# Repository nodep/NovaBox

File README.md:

# NovaBox

This repo contains circuit and PCB designs for Bluetooth amplifiers

### Why build yet another Bluetooth speaker?

The main motivation for this project was the fact that I needed a Bluetooth speaker with batteries that are easy to remove and replace. Most of the commercial Bluetooth speakers have a charging port, and when you run out of battery power the device has to be connected to a charger for several hours. With removable batteries it takes ten seconds to go from empty to full if you have a spare battery. Even though CSR8635 needs only a few components to be able to charge Li-ion batteries, an integrated charger would make the PCB larger, there would be problems with heat dissipation during charging, and charging a medium capacity 18650 battery would take too long.

## The circuit

The circuit is based around the CSR8635 module you can get on most Chinese on-line shops. Its model number is BT835.

### Schematic and PCB

The circuit and PCB are designed in KiCad v5. The project contains all the symbols in its own symbol library (NovaBox.lib) and all the footprints (NovaBox.pretty). The schematic only references power symbols (GND, VCC, Batt, 5V) from the KiCad libraries. The circuit schematic is also saved in PDF [here](docs/NovaBox_8635.pdf).

The PCB has two layers with components soldered on both sides.

### Circuit sections

The circuit has several subsections:

* A single unprotected Li-ion 18650 battery with reverse protection and reverse indicator LED, and a hard on/off switch brought out to a pin header.
* The CSR8635 module with five buttons brought out to pin headers, an RGD LED driven from the module's 3 LED pins, and CSR8635's USB pins brought out to a THT Mini USB connector. The buttons can be configured for any of the standard commands: play/pause, next, volume up/down and so on.
* A section providing a pulse on CSR8635's PWER_E pin which wakes it up after the circuit has received power.
* The power section with an [LT1308](docs/LT1308abfb.pdf) DC/DC converter which boost the battery voltage to 5V at max 1A. The power section is disabled when CSR8635 goes to shutdown on low battery (< 3.2V). LT1308 has a soft-start feature which is implemented in the design, but is not necessary for the operation of the rest of the power section.
* A four level battery charge indicator with four LEDs which is built around a quad op-amp [MCP6004](docs/MCP6004.pdf). The op-amps work as comparators with inputs from four voltage dividers, comparing them to a 2.5V reference [LM4040](docs/lm4040-n.pdf). The op-amp outputs drive the four LEDs.
* The audio amplifier section is built around two [PAM8304](docs/PAM8304.pdf). The amplifiers can drive two 8Ω speakers at 1.7W each. They can also drive 4Ω speakers at 3W each, but the sum power requirement of the amplifiers would exceed the 5W that LT1308 can provide.
 
## Flash configuration

The SPI configuration interface of the CSR8635 module is brought out to a 5 pin header. This can be used to configure various parameters of the system such as device name, button mapping, RGB LED states, etc.

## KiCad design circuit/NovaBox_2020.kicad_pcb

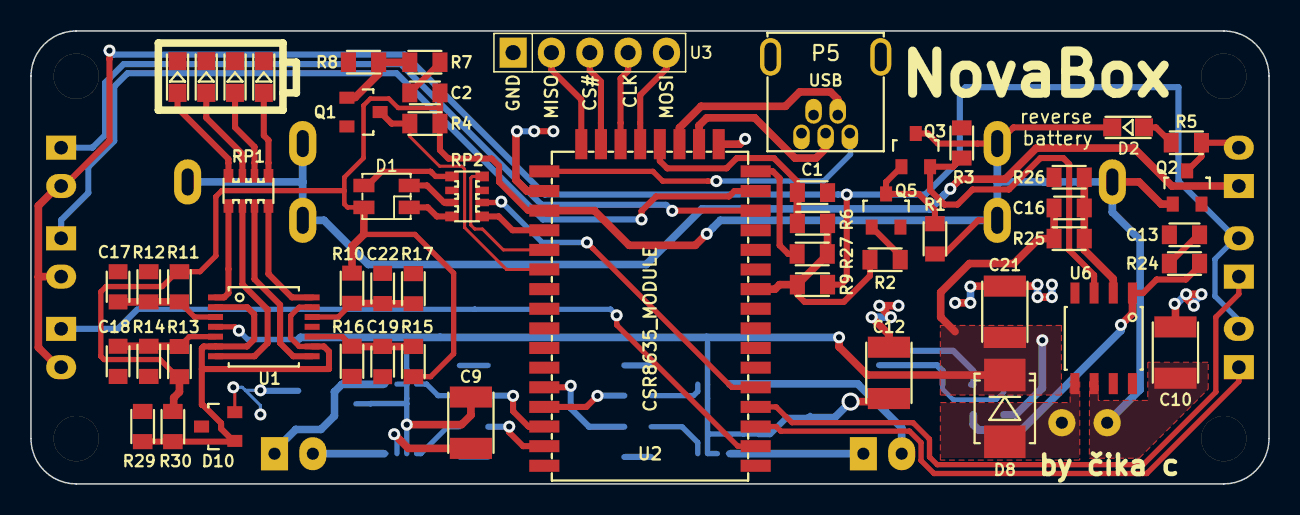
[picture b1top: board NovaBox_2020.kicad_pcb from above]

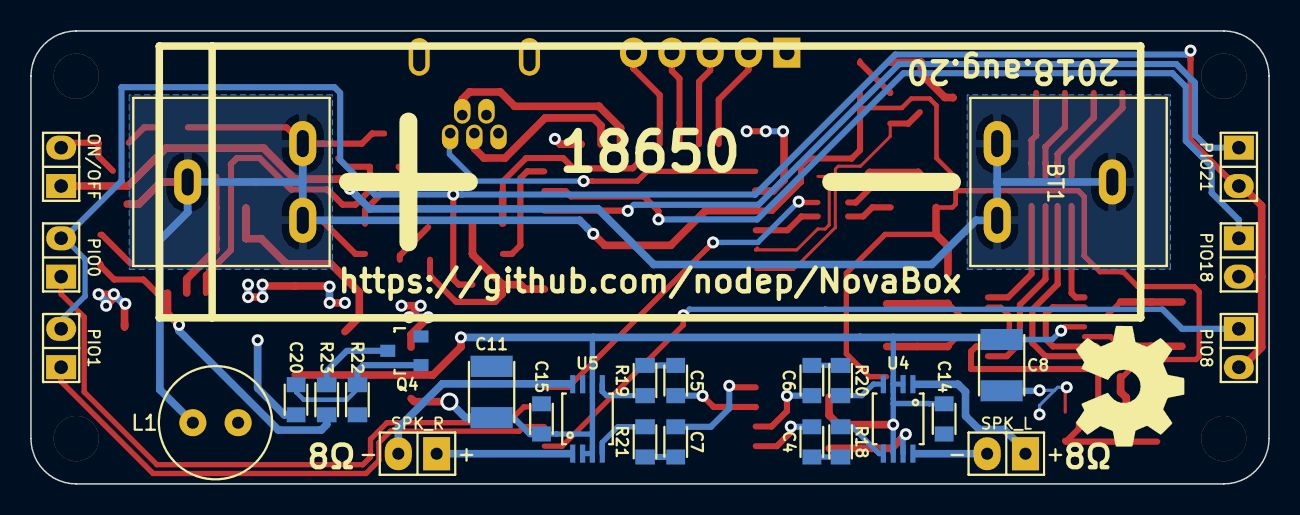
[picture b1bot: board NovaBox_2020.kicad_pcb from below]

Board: 2 copper layers, 82.0 x 30.0 mm, 86 parts (28 on the bottom side), 69 nets.

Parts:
BT1: 18650; Batt_Holder_18650
C1: 100nF; C_0805
C2, C4, C5, C6, C7, C14, C15, C17, C18, C19, C22: 1uF; C_0805
C8, C9, C10, C11, C12, C21: 47uF; C_1210
C13: 100pF; C_0805
C16: 330pF; C_0805
C20: 33nF; C_0805
D1: LED_RABG; PLCC4
D2: REVERSE_BATT; LED_0805
D4: BATT_E; LED_0805
D5: BATT_L; LED_0805
D6: BATT_M; LED_0805
D7: BATT_H; LED_0805
D8: MBRS130LT3; SMB_403A
D10: Vref 2.5V; SOT-23
L1: 4.7uH; COIL0608
P1, P2, P3, P4: MH; MountingHole
P5: USB; USB_MiniB_THT
Q1, Q4, Q5: MMBT3904; SOT-23
Q2: IRLML6344; SOT-23
Q3: IRLML6401; SOT-23
R1, R2, R3, R4, R6, R8, R18, R19, R20, R21, R27, R29: 10K; R_0805
R5, R7, R9: 1K; R_0805
R10, R13: 270K; R_0805
R11, R15: 240K; R_0805
R12, R14: 620K; R_0805
R16, R17: 470K; R_0805
R22, R23: 33K; R_0805
R24: 47K; R_0805
R25: 316K; R_0805
R26: 100K; R_0805
R30: 750; R_0805
RP1, RP2: R_Pack04; Resistor_Array_x4_1206
S1: SPK_L; SPKR
S2: SPK_R; SPKR
SW1: PIO18; Switch_2.5mm
SW2: PIO21; Switch_2.5mm
SW3: PIO8; Switch_2.5mm
SW4: PIO0; Switch_2.5mm
SW5: PIO1; Switch_2.5mm
SW6: ON/OFF; Switch_2.5mm
U1: MCP6004; TSSOP-14_4.4x5mm_Pitch0.65mm
U2: CSR8635_MODULE
U3: CSR_DebugSmall
U4, U5: PAM8304; MSOP-8_0.65mmPitch
U6: LT1308; SOIC-8_3.9x4.9mm_Pitch1.27mm

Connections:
1V8: R2.2, R6.1, R9.1, R27.1, U2.10
2V5: D10.1, R29.2, R30.1, U1.2, U1.6, U1.9, U1.13
+5V: C8.1, C9.1, C11.1, C12.1, C14.1, C15.1, C16.1, C20.2, C21.1, D8.1, R25.1, U1.4, U4.2, U4.3, U4.6, U5.2, U5.3, U5.6
+BATT: BT1.1, C2.1, C10.1, D1.2, D2.1, L1.2, Q2.1, Q3.3, R1.1, R4.2, R10.2, R11.2, R13.2, R15.2, R30.2, U2.27, U6.6
/-BATT: BT1.2, SW6.1
/D+: P5.3, U2.18
/D-: P5.2, U2.19
/FB: C16.2, R25.2, R26.1, U6.2
/SW: D8.2, L1.1, U6.5
CSR_RST: C1.1, R6.2, U2.20
GND: C1.2, C8.2, C9.2, C10.2, C11.2, C12.2, C13.2, C14.2, C15.2, C17.2, C18.2, C19.2, C21.2, C22.2, D4.1, D5.1, D6.1, D7.1, D10.2, P5.5, Q1.2, Q2.2, Q4.2, Q5.2, R3.2, R8.1, R12.2, R14.2, R16.2, R17.2, R22.2, R26.2, R29.1, U1.11, U2.17, U2.26, U2.40, U3.5, U4.7, U5.7, U6.4
LED0: RP2.1, U2.28
LED1: RP2.2, U2.5
LED2: RP2.4, U2.29
unnamed: C2.2, R7.2
unnamed: C4.1, R18.1
unnamed: C4.2, U2.39
unnamed: C5.1, R19.1
unnamed: C5.2, U2.37
unnamed: C6.1, R20.1
unnamed: C6.2, U2.38
unnamed: C7.1, R21.1
unnamed: C7.2, U2.36
unnamed: C13.1, R24.2
unnamed: C17.1, R11.1, R12.1, U1.3
unnamed: C18.1, R13.1, R14.1, U1.5
unnamed: C19.1, R15.1, R16.1, U1.10
unnamed: C20.1, Q4.1, R22.1
unnamed: C22.1, R10.1, R17.1, U1.12
unnamed: D1.1, RP2.8
unnamed: D1.3, RP2.5
unnamed: D1.4, RP2.7
unnamed: D2.2, R5.2
unnamed: D4.2, RP1.8
unnamed: D5.2, RP1.7
unnamed: D6.2, RP1.6
unnamed: D7.2, RP1.5
unnamed: Q1.1, R7.1, R8.2
unnamed: Q2.3, R5.1, SW6.2
unnamed: Q3.1, Q5.3, R1.2
unnamed: Q4.3, R23.2
unnamed: Q5.1, R2.1
unnamed: R9.2, SW1.2, SW2.2, SW3.2, SW4.2, SW5.2
unnamed: R18.2, U4.5
unnamed: R19.2, U5.5
unnamed: R20.2, U4.4
unnamed: R21.2, U5.4
unnamed: R23.1, R24.1, U6.1
unnamed: RP1.1, U1.1
unnamed: RP1.2, U1.7
unnamed: RP1.3, U1.8
unnamed: RP1.4, U1.14
unnamed: S1.1, U4.1
unnamed: S1.2, U4.8
unnamed: S2.1, U5.1
unnamed: S2.2, U5.8
unnamed: U2.21, U3.1
unnamed: U2.22, U3.2
unnamed: U2.23, U3.3
unnamed: U2.24, U3.4
PIO0: SW4.1, U2.4
PIO1: SW5.1, U2.3
PIO8: SW3.1, U2.2
PIO18: SW1.1, U2.15
PIO21: SW2.1, U2.14
PWER_E: Q1.3, R4.1, U2.30
SPI_PCM: R27.2, U2.16
VBUS: P5.1, U2.25
VR_SHDN: Q3.2, R3.1, U6.3

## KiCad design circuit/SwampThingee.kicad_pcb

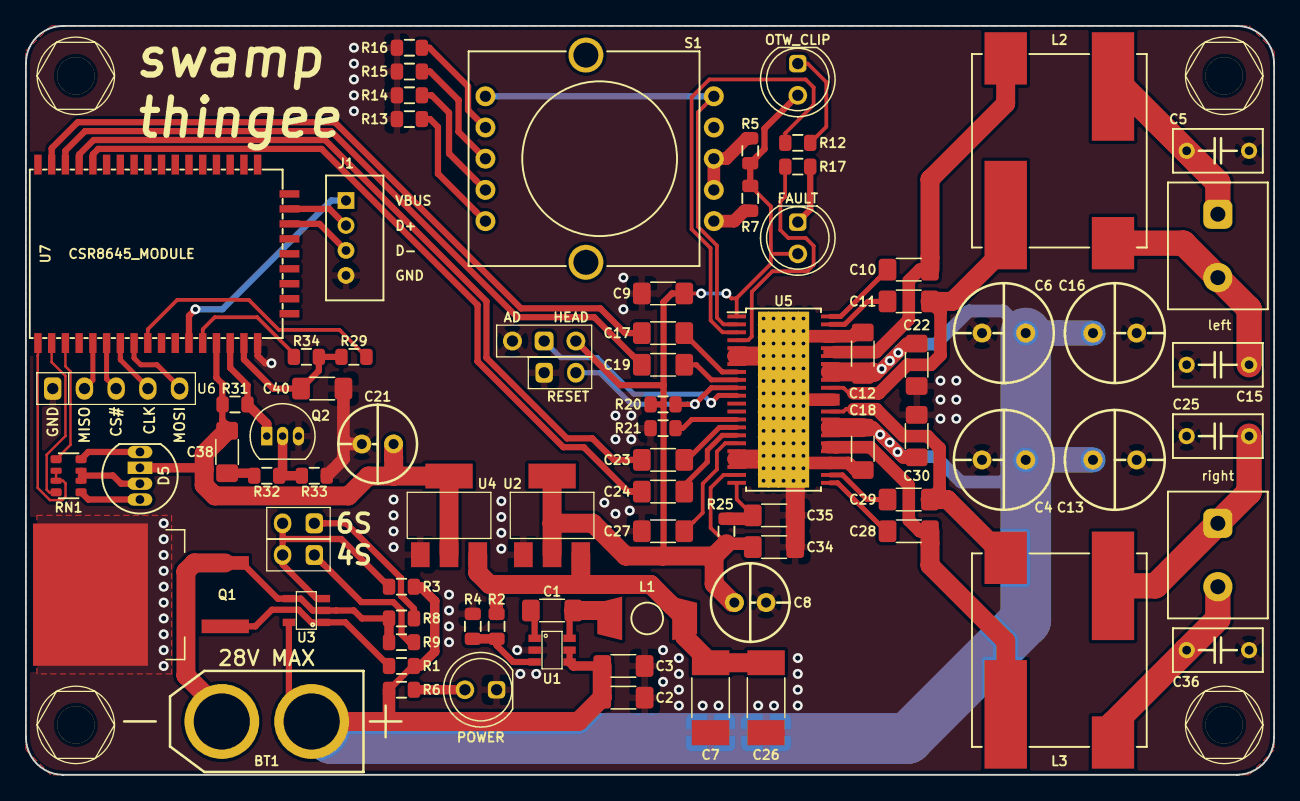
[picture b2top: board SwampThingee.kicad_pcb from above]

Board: 2 copper layers, 100.0 x 60.0 mm, 86 parts (0 on the bottom side), 69 nets.

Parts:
BT1: 28V MAX; XT60-M-NO_PM
C1, C3, C9, C40: 100nF; C_1206
C2: 4.7μF; C_1206
C4, C6, C13, C16: 470μF; CPOL_D8_P3.5
C5, C15, C25, C36: 1μF; C_FILM_5MM
C7, C26: 15μF; C_1812
C8: 470μF; CPOL_D6.3_P2.5
C10, C11, C27, C28, C29: 33nF; C_1206
C12, C17, C18, C19, C22, C23, C24, C30, C34, C35, C38: 1μF; C_1206
C21: 100μF; CPOL_D6.3_P2.5
D2: OTW_CLIP; LED_D5.0mm
D3: POWER; LED_D5.0mm
D4: FAULT; LED_D5.0mm
D5: LED_RABG; LED_D5.0mm_RGB
J1: CONN_01X04; PIN_1x4_P2.00mm
J2, J3, J4, J5: HOLE; MountingHole
L1: 68μH; COIL_SRR6603
L2, L3: 10μH; COILCRAFT-UA801x-AL
Q1: IRFS52N15DTRLP; TO-263-2
Q2: BC547; TO-92_Inline_Narrow_Oval
R1, R6, R29, R31, R33, R34: 10K; R_0805
R2: 133K; R_0805
R3: 1.69M; R_0805
R4: 22.1K; R_0805
R5: 100K; R_0805
R7: 75K; R_0805
R8: 105K; R_0805
R9: 162K; R_0805
R12, R17, R32: 1K; R_0805
R13: 5.6K; R_0805
R14: 20K; R_0805
R15: 39K; R_0805
R16, R20: 47K; R_0805
R21: 50K; R_0805
R25: 3.3R; R_0805
RN1: 1K; Resistor_Array_x4_1206
S1: GAIN_SEL; SR1712F-0204-20F0A-N9-N-027
SPK1: left; SPKR_5MM_BLUE
SPK2: right; SPKR_5MM_BLUE
SW1: RESET; Switch_2.5mm
SW3: HEAD/AD; SW_SPDT_JUMPER
SW9: 6S; Switch_2.5mm
SW10: 4S; Switch_2.5mm
U1: TPS560430; SOT-23-6
U2: LM1117-5.0; SOT-223
U3: MAX6457; SOT-23-5
U4: LM1117-3.3; SOT-223
U5: TPA3220; TSSOP-44_4.4x9.7mm_Pitch0.635mm_ThermalPad
U6: CSR_DebugSmall
U7: CSR8645_MODULE

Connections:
1V8: C40.2, R29.1, R34.1, U7.16
+3V3: C21.1, C38.1, D5.2, R31.2, U4.2, U7.14
+5V: C8.1, C9.2, C34.1, D2.2, D4.2, R5.1, R7.1, R20.2, R25.2, SW3.1, U2.2, U5.1, U5.21
+7.5V: C7.2, C26.2, L1.2, R2.1, U2.3, U4.3
+BATT: BT1.1, C2.2, C3.2, C4.1, C6.1, C12.2, C13.1, C16.1, C18.1, C22.1, C30.1, R1.2, R3.1, R6.1, U1.4, U1.5, U3.5, U5.29, U5.30, U5.31, U5.36, U5.37, U5.38
-BATT: BT1.2, Q1.3, R8.2, R9.2, U3.2, U3.4
/BLU: RN1.6, RN1.7, U7.1
/CLK: U6.2, U7.7
/CMUTE: C27.1, U5.17
/CS#: U6.3, U7.6
/FREQ_ADJ: R21.2, U5.14
/GAIN_SLV: S1.1, S1.10, U5.2
/GRN: RN1.8, U7.2
/GVDD: C35.1, R25.1, U5.22
/MAX_VDIV: R3.2, SW9.2, SW10.2, U3.3
/MISO: U6.4, U7.5
/MOSI: U6.1, U7.8
/OUT1_M: C11.2, L2.1, U5.35
/OUT1_P: C10.2, L2.4, U5.39, U5.40
/OUT2_M: C28.1, L3.1, U5.27, U5.28
/OUT2_P: C29.1, L3.4, U5.32
/PWER_E: Q2.1, R31.1, U7.15
/RED: RN1.5, U7.3
/RESET: R20.1, SW1.2, U5.10
/RST: R34.2, U7.13
/SPI_PCM: R29.2, U7.9
/SW_GATE: Q1.1, R1.1, U3.1
/USB_D+: J1.2, U7.25
/USB_D-: J1.3, U7.24
FAULT: R17.1, U5.4
GND: C2.1, C3.1, C4.2, C5.2, C6.2, C7.1, C8.2, C9.1, C12.1, C13.2, C15.1, C16.2, C18.2, C21.2, C22.2, C25.2, C26.1, C27.2, C30.2, C34.2, C35.2, C36.1, C40.1, D3.1, J1.4, Q1.2, Q2.3, R4.2, R13.2, R14.2, R15.2, R16.2, R21.1, R33.1, SW1.1, SW3.3, U1.2, U2.1, U4.1, U5.5, U5.6, U5.7, U5.18, U5.19, U5.20, U5.25, U5.26, U5.33, U5.34, U5.41, U5.42, U5.45, U6.5, U7.17
HEAD: SW3.2, U5.11
unnamed: C1.1, L1.1, U1.6
unnamed: C1.2, U1.1
unnamed: C5.1, L2.3, SPK1.1
unnamed: C10.1, U5.44
unnamed: C11.1, U5.43
unnamed: C15.2, L2.2, SPK1.2
unnamed: C17.2, U5.8
unnamed: C19.2, U5.9
unnamed: C23.2, U5.15
unnamed: C24.2, U5.16
unnamed: C25.1, L3.3, SPK2.1
unnamed: C28.2, U5.23
unnamed: C29.2, U5.24
unnamed: C36.2, L3.2, SPK2.2
unnamed: C38.2, R32.2
unnamed: D2.1, R12.2
unnamed: D3.2, R6.2
unnamed: D4.1, R17.2
unnamed: D5.1, RN1.4
unnamed: D5.3, RN1.2, RN1.3
unnamed: D5.4, RN1.1
unnamed: Q2.2, R32.1, R33.2
unnamed: R2.2, R4.1, U1.3
unnamed: R5.2, S1.3, S1.4
unnamed: R7.2, S1.5
unnamed: R8.1, SW9.1
unnamed: R9.1, SW10.1
unnamed: R13.1, S1.6
unnamed: R14.1, S1.7
unnamed: R15.1, S1.8
unnamed: R16.1, S1.9
OTW_CLIP: R12.1, U5.3
SPK_LN: C19.1, U7.41
SPK_LP: C17.1, U7.42
SPK_RN: C24.1, U7.39
SPK_RP: C23.1, U7.40
VBUS: J1.1, U7.12

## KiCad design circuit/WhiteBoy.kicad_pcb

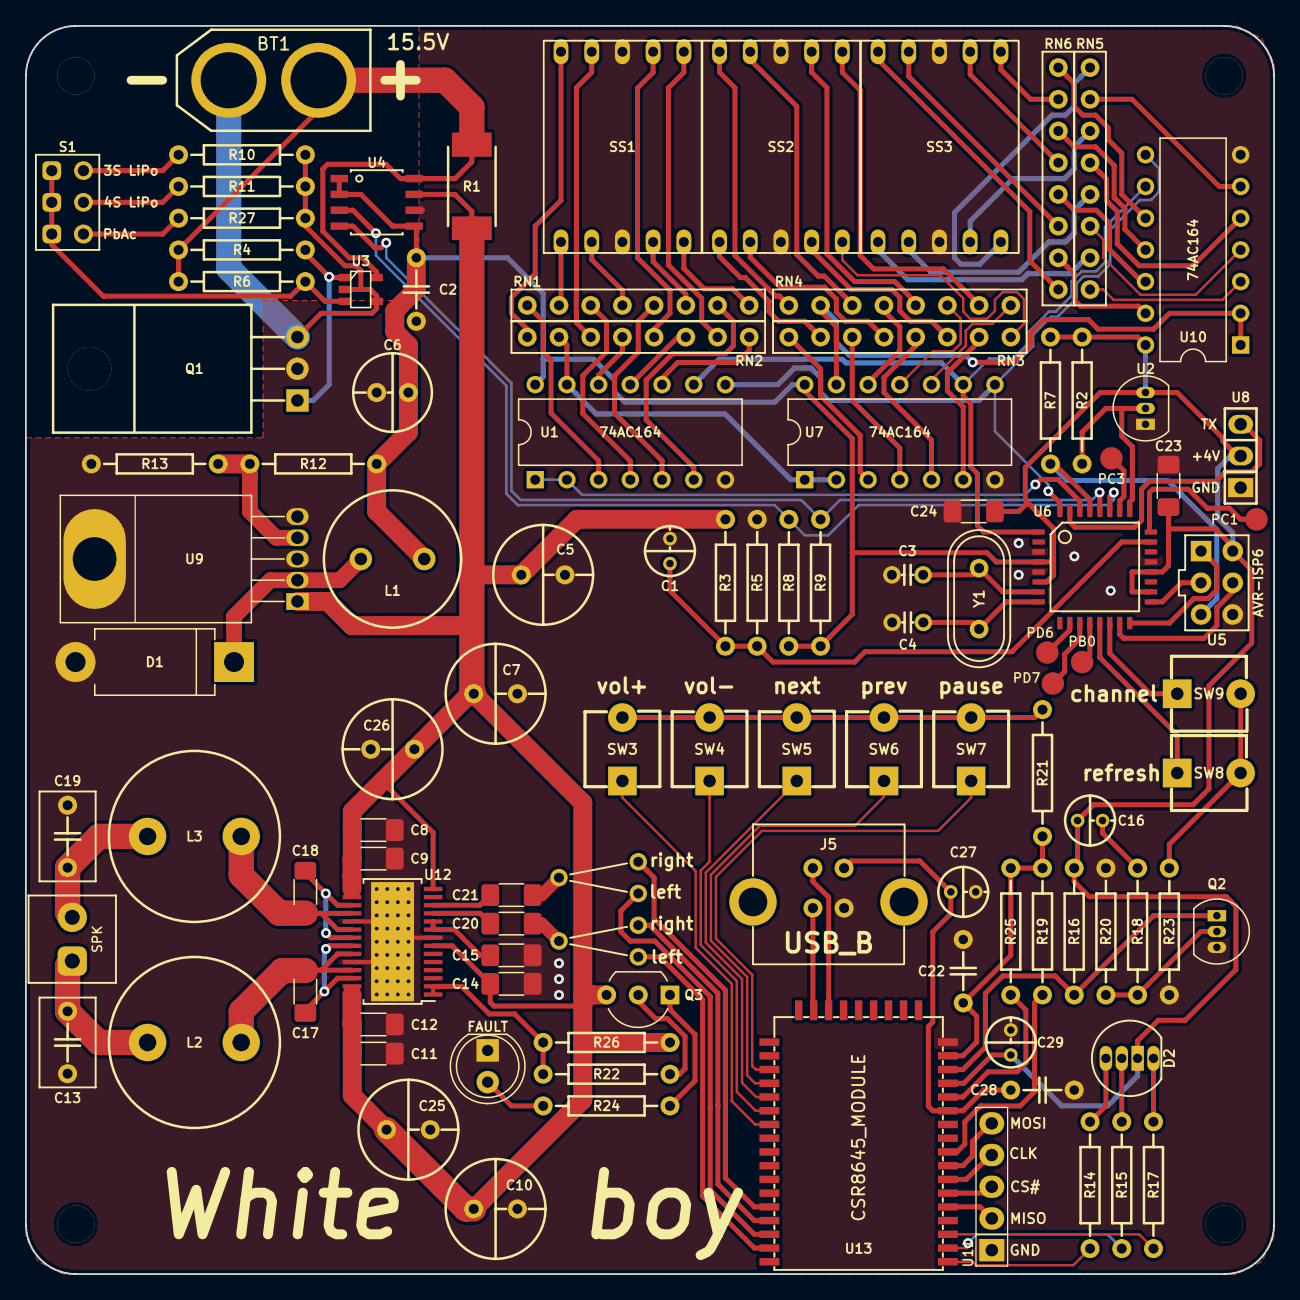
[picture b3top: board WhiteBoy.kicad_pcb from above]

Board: 2 copper layers, 100.0 x 100.0 mm, 110 parts (0 on the bottom side), 126 nets.

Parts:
BT1: 15.5V; XT60-M
C1, C16, C27, C29: 1uF; CPOL_D4_P2
C2, C22, C28: 100nF; C_5MM
C3, C4: 22pF; C_2.5MM
C5: 100μF; CPOL_D8_P3.5
C6: 100μF; CPOL_D6.3_P2.5
C7, C10, C25, C26: 220μF; CPOL_D8_P3.5
C8, C11: 100nF; C_1206
C9, C12: 1nF; C_1206
C13, C19: 680nF; C_FILM_5MM
C14, C15, C20, C21, C23, C24: 1uF; C_1206
C17, C18: 470nF; C_1206
D1: 1N5822; DO-201AD_P12.70mm_Horizontal
D2: LED_RABG; LED_D5.0mm_RGB
D5: FAULT; LED_D5.0mm
J1, J2, J3, J4: HOLE; MountingHole
J5: USB_B; USB_B_VERT
L1: 680μH; COIL_LHL10TB681K
L2, L3: 10μH; COILCRAFT_RFS1412
Q1: IRF530NPbF; TO-220_Horizontal
Q2: BC547; TO-92_Inline_Narrow_Oval
Q3: BC557; TO-92_Inline_Wide
R1: 0.075R; R_2512
R2, R8, R9: 4K7; R_10MM
R3, R12: 2K7; R_10MM
R4, R7, R16, R19, R20, R25, R26: 10K; R_10MM
R5, R18, R22, R23, R24: 1K; R_10MM
R6: 1M69; R_10MM
R10: 226K; R_10MM
R11: 162K; R_10MM
R13: 1K2; R_10MM
R14, R15, R17, R21: 470; R_10MM
R27: 187K; R_10MM
RN1, RN2, RN3, RN4, RN5, RN6: 100R; RN4_P2.54
S1: BATT_SEL
S2: SPK; SPKR_BIG
SS1, SS2, SS3: SEVSEG; 7seg_14.2mm
SW1: POS; SW_SPDT
SW2: NEG; SW_SPDT
SW3: vol+; Tact_6x6
SW4: vol-; Tact_6x6
SW5: next; Tact_6x6
SW6: prev; Tact_6x6
SW7: pause; Tact_6x6
SW8: refresh; Tact_6x6
SW9: channel; Tact_6x6
T1: PB0; TestPad
T4: PC1; TestPad
T5: PC3; TestPad
T6: PD6; TestPad
T7: PD7; TestPad
U1, U7, U10: 74AC164; DIP-14_W7.62mm
U2: DS18B20; TO-92_Inline_Narrow_Oval
U3: MAX6457; SOT-23-5
U4: INA219_SOIC; SOIC-8_3.9x4.9mm_Pitch1.27mm
U5: AVR-ISP6; AVR_ISP6
U6: ATMEGA88PA-16AU; TQFP-32_7x7mm_Pitch0.8mm
U8: DBG; DBG_TX
U9: LM2576T-ADJ; TO-220-5_Horizontal
U11: CSR_CFG; CSR_DebugSmall
U12: TPA3136D2; HTSSOP-28_4.4x9.7mm_Pitch0.65mm_ThermalPad
U13: CSR8645_MODULE
Y1: 16MHz; Crystal_HC49-U_Vertical

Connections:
1V8: C22.2, R19.1, R21.1, R25.1, U13.16
+4V: C2.2, C6.1, C16.1, C23.1, C24.1, C29.1, D2.2, L1.2, R2.1, R7.2, R8.2, R9.2, R12.1, R16.2, U1.14, U2.3, U4.1, U4.2, U4.5, U5.2, U6.4, U6.6, U6.18, U6.20, U7.14, U8.2, U10.14, U13.14
+BATT: BT1.1, R1.2, R4.2, R6.1, U3.5, U4.8
-BATT: BT1.2, Q1.3, R10.2, R11.2, R27.2, U3.2, U3.4
/GVDD: C15.1, U12.9, U12.10
/MAX_VDIV: R6.2, S1.1, U3.3
/NEXT: SW5.1, U13.31
/OUTL: C17.1, L2.1, U12.23, U12.25
/OUTR: C18.1, L3.1, U12.18, U12.20
/PAUSE: SW7.1, U13.29
/PREV: SW6.1, U13.30
/PWER_E: Q2.1, R16.1, U13.15
/SD_FAULT: R22.1, R26.2, U12.1, U12.2
/SPI_PCM: R19.2, U13.9
/SPK_LN: SW1.1, U13.41
/SPK_LP: SW2.1, U13.42
/SPK_RN: SW1.3, U13.39
/SPK_RP: SW2.3, U13.40
/SW_GATE: Q1.1, R4.1, U3.1
/VOL+: SW3.1, U13.33
/VOL-: SW4.1, U13.32
AVR_RST: R7.1, U5.5, U6.29
BATT_SNS: C1.1, R3.2, R5.1, U6.23
BT_NEG: C20.2, SW2.2
BT_POS: C21.2, SW1.2
DS18_DQ: R2.2, U2.2, U6.25
GND: C1.2, C2.1, C3.2, C4.2, C5.2, C6.2, C7.2, C8.2, C9.2, C10.2, C11.2, C12.2, C13.1, C14.2, C15.2, C19.2, C22.1, C23.2, C24.2, C25.2, C26.2, C27.2, C28.1, C29.2, D1.2, D5.1, J5.4, Q1.2, Q2.3, R5.2, R13.2, R20.1, R23.1, SS1.3, SS1.8, SS2.3, SS2.8, SS3.3, SS3.8, U1.7, U2.1, U4.6, U5.6, U6.3, U6.5, U6.21, U7.7, U8.1, U9.3, U9.5, U10.7, U11.5, U12.8, U12.19, U12.24, U12.29, U13.17
LED_CK: U1.8, U6.32, U7.8, U10.8
LED_DT: U1.1, U1.2, U6.30
LED_RST: U1.9, U6.1, U7.9, U10.9
unnamed: C3.1, U6.7, Y1.1
unnamed: C4.1, U6.8, Y1.2
unnamed: C13.2, L2.2, S2.1
unnamed: C16.2, R18.2
unnamed: C17.2, U12.22, U12.26
unnamed: C18.2, U12.17, U12.21
unnamed: C19.1, L3.2, S2.2
unnamed: C20.1, U12.11
unnamed: C21.1, U12.12
unnamed: D1.1, L1.1, U9.2
unnamed: D2.1, R17.2
unnamed: D2.3, R15.2
unnamed: D2.4, R14.2
unnamed: D5.2, R24.2
unnamed: J5.2, U13.24
unnamed: J5.3, U13.25
unnamed: Q2.2, R18.1, R20.2
unnamed: Q3.1, R24.1
unnamed: Q3.2, R22.2
unnamed: R10.1, S1.2
unnamed: R11.1, S1.3
unnamed: R12.2, R13.1, U9.4
unnamed: R14.1, U13.1
unnamed: R15.1, U13.2
unnamed: R17.1, U13.3
unnamed: R21.2, SW3.2, SW4.2, SW5.2, SW6.2, SW7.2
unnamed: R23.2, SW8.2, SW9.2
unnamed: R25.2, U13.13
unnamed: R27.1, S1.4
unnamed: RN1.1, U1.3
unnamed: RN1.2, SS1.1
unnamed: RN1.3, U1.4
unnamed: RN1.4, SS1.2
unnamed: RN1.5, U1.5
unnamed: RN1.6, SS1.4
unnamed: RN1.7, U1.6
unnamed: RN1.8, SS1.5
unnamed: RN2.1, U1.10
unnamed: RN2.2, SS1.6
unnamed: RN2.3, U1.11
unnamed: RN2.4, SS1.7
unnamed: RN2.5, U1.12
unnamed: RN2.6, SS1.9
unnamed: RN2.7, U1.13, U7.1, U7.2
unnamed: RN2.8, SS1.10
unnamed: RN3.1, U7.3
unnamed: RN3.2, SS2.1
unnamed: RN3.3, U7.4
unnamed: RN3.4, SS2.2
unnamed: RN3.5, U7.5
unnamed: RN3.6, SS2.4
unnamed: RN3.7, U7.6
unnamed: RN3.8, SS2.5
unnamed: RN4.1, U7.10
unnamed: RN4.2, SS2.6
unnamed: RN4.3, U7.11
unnamed: RN4.4, SS2.7
unnamed: RN4.5, U7.12
unnamed: RN4.6, SS2.9
unnamed: RN4.7, U7.13, U10.1, U10.2
unnamed: RN4.8, SS2.10
unnamed: RN5.1, U10.3
unnamed: RN5.2, SS3.1
unnamed: RN5.3, U10.4
unnamed: RN5.4, SS3.2
unnamed: RN5.5, U10.5
unnamed: RN5.6, SS3.4
unnamed: RN5.7, U10.6
unnamed: RN5.8, SS3.5
unnamed: RN6.1, U10.10
unnamed: RN6.2, SS3.6
unnamed: RN6.3, U10.11
unnamed: RN6.4, SS3.7
unnamed: RN6.5, U10.12
unnamed: RN6.6, SS3.9
unnamed: RN6.7, U10.13
unnamed: RN6.8, SS3.10
unnamed: SW8.1, U6.13
unnamed: SW9.1, U6.14
unnamed: T1.1, U6.12
unnamed: T4.1, U6.24
unnamed: T5.1, U6.26
unnamed: T6.1, U6.10
unnamed: T7.1, U6.11
unnamed: U5.1, U6.16
unnamed: U5.3, U6.17
unnamed: U5.4, U6.15
unnamed: U6.31, U8.3
unnamed: U11.1, U13.8
unnamed: U11.2, U13.7
unnamed: U11.3, U13.6
unnamed: U11.4, U13.5
SCL: R9.1, U4.4, U6.28
SDA: R8.1, U4.3, U6.27
VBUS: C27.1, C28.2, J5.1, U13.12
VDD: C5.1, C7.1, C8.1, C9.1, C10.1, C11.1, C12.1, C14.1, C25.1, C26.1, Q3.3, R1.1, R3.1, R26.1, U4.7, U9.1, U12.7, U12.14, U12.15, U12.16, U12.27, U12.28

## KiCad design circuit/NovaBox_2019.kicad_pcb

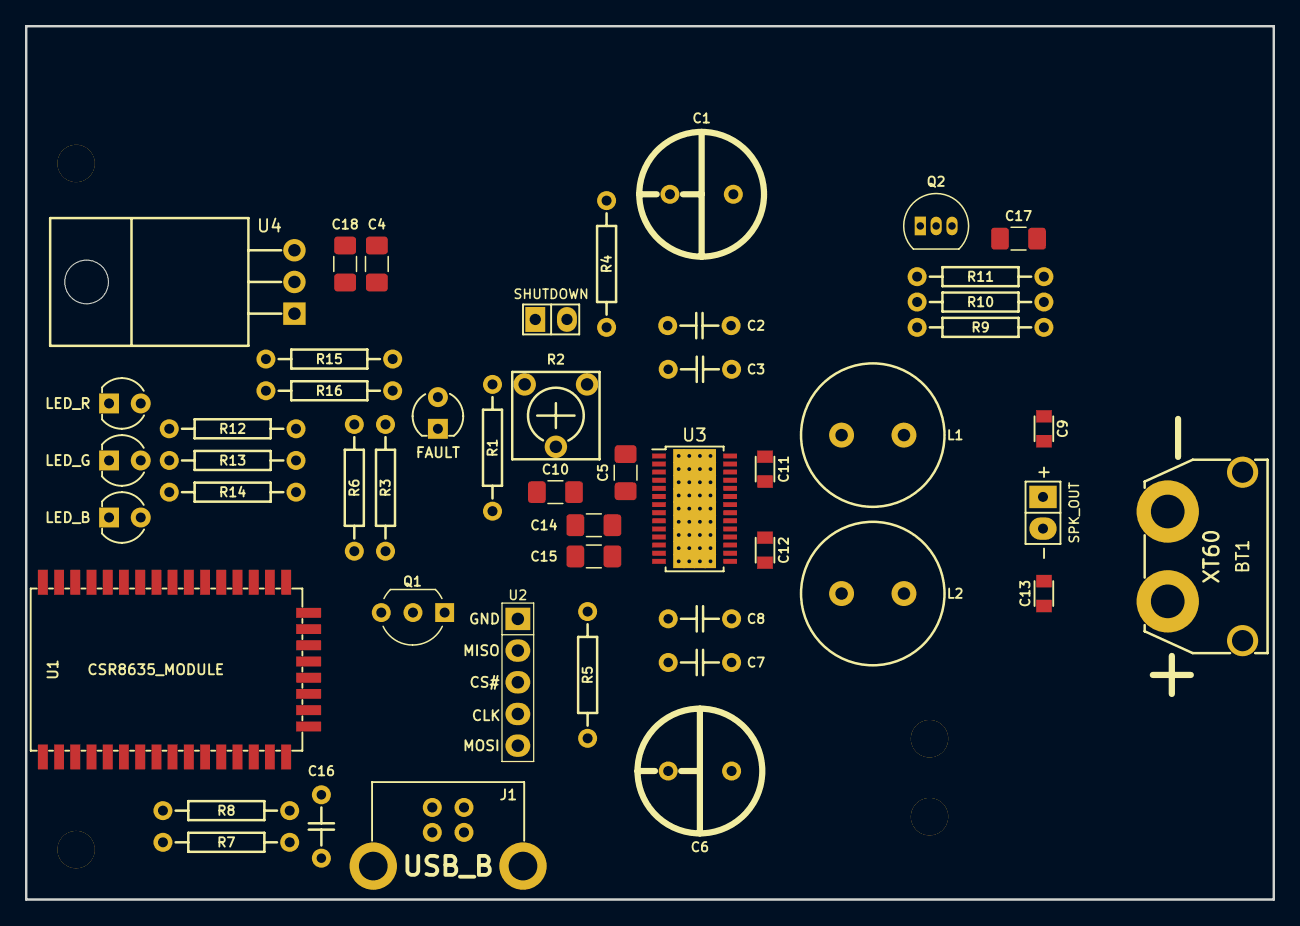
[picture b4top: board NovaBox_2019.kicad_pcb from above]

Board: 2 copper layers, 100.0 x 70.0 mm, 54 parts (0 on the bottom side), 41 nets, no tracks yet.

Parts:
BT1: XT60; XT60PW-M
C1, C6: 100uF; CPOL_D10_P4.5
C2, C7, C16: 100nF; C_5MM
C3, C8: 1nF; C_5MM
C4, C5, C10, C14, C15, C17, C18: 1uF; C_1206
C9, C13: 680nF; C_0805
C11, C12: 470nF; C_0805
D1: FAULT; LED-3MM
D2: LED_R; LED-3MM
D3: LED_G; LED-3MM
D4: LED_B; LED-3MM
J1: USB_B
J2, J3, J4, J5: HOLE; MountingHole
L1, L2: 10uH; Inductor_5mm
Q1: BC557; TO-92_Inline_Wide
Q2: BC547; TO-92_Inline_Narrow_Oval
R1, R3: 10k; R_10MM
R2: 100k; RPOT_RKT6V
R4, R5: 100k; R_10MM
R6, R15, R16: 1k; R_10MM
R7, R8, R9, R11: 10K; R_10MM
R10, R12, R13, R14: 1K; R_10MM
S1: SHUTDOWN; Switch_2.5mm
SPK1: SPK_OUT; SPKR
U1: CSR8635_MODULE
U2: CSR_DebugSmall
U3: TPA3136D2; HTSSOP-28_4.4x9.7mm_Pitch0.65mm_ThermalPad
U4: LM317; TO-220_Horizontal

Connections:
+1V8: R7.1, R8.1, U1.10
+4V: C4.1, C17.1, D2.2, D3.2, D4.2, R9.2, R15.1, U1.27, U4.2
+12V: BT1.1, C1.1, C2.2, C3.2, C5.2, C6.1, C7.2, C8.2, C18.1, D1.2, R3.1, R4.2, R5.2, U3.7, U3.15, U3.16, U3.27, U3.28, U4.3
/D+: J1.3, U1.18
/D-: J1.2, U1.19
CSR_RST: C16.1, R8.2, U1.20
GND: BT1.2, C1.2, C2.1, C3.1, C4.2, C5.1, C6.2, C7.1, C8.1, C9.1, C10.1, C13.1, C16.2, C18.2, J1.4, Q1.1, Q2.3, R1.2, R11.1, R16.2, S1.1, U1.17, U1.26, U1.40, U2.5, U3.8, U3.19, U3.24, U3.29
LED_B: R14.1, U1.29
LED_G: R13.1, U1.5
LED_R: R12.1, U1.28
MFB: Q2.1, R9.1, U1.30
unnamed: C9.2, L1.2, SPK1.1
unnamed: C10.2, R2.1, U3.9
unnamed: C11.1, L1.1, U3.23, U3.25
unnamed: C11.2, U3.22, U3.26
unnamed: C12.1, L2.1, U3.18, U3.20
unnamed: C12.2, U3.17, U3.21
unnamed: C13.2, L2.2, SPK1.2
unnamed: C14.2, U3.11
unnamed: C15.2, U3.12
unnamed: C17.2, R10.2
unnamed: D1.1, R6.1
unnamed: D2.1, R12.2
unnamed: D3.1, R13.2
unnamed: D4.1, R14.2
unnamed: Q1.2, R3.2, U3.2
unnamed: Q1.3, R6.2
unnamed: Q2.2, R10.1, R11.2
unnamed: R1.1, R2.3
unnamed: R2.2, U3.10
unnamed: R4.1, S1.2, U3.1
unnamed: R5.1, U3.14
unnamed: R15.2, R16.1, U4.1
unnamed: U1.21, U2.1
unnamed: U1.22, U2.2
unnamed: U1.23, U2.3
unnamed: U1.24, U2.4
SPI_PCM: R7.2, U1.16
SPK_RN: C14.1, U1.36
SPK_RP: C15.1, U1.37
VBUS: J1.1, U1.25

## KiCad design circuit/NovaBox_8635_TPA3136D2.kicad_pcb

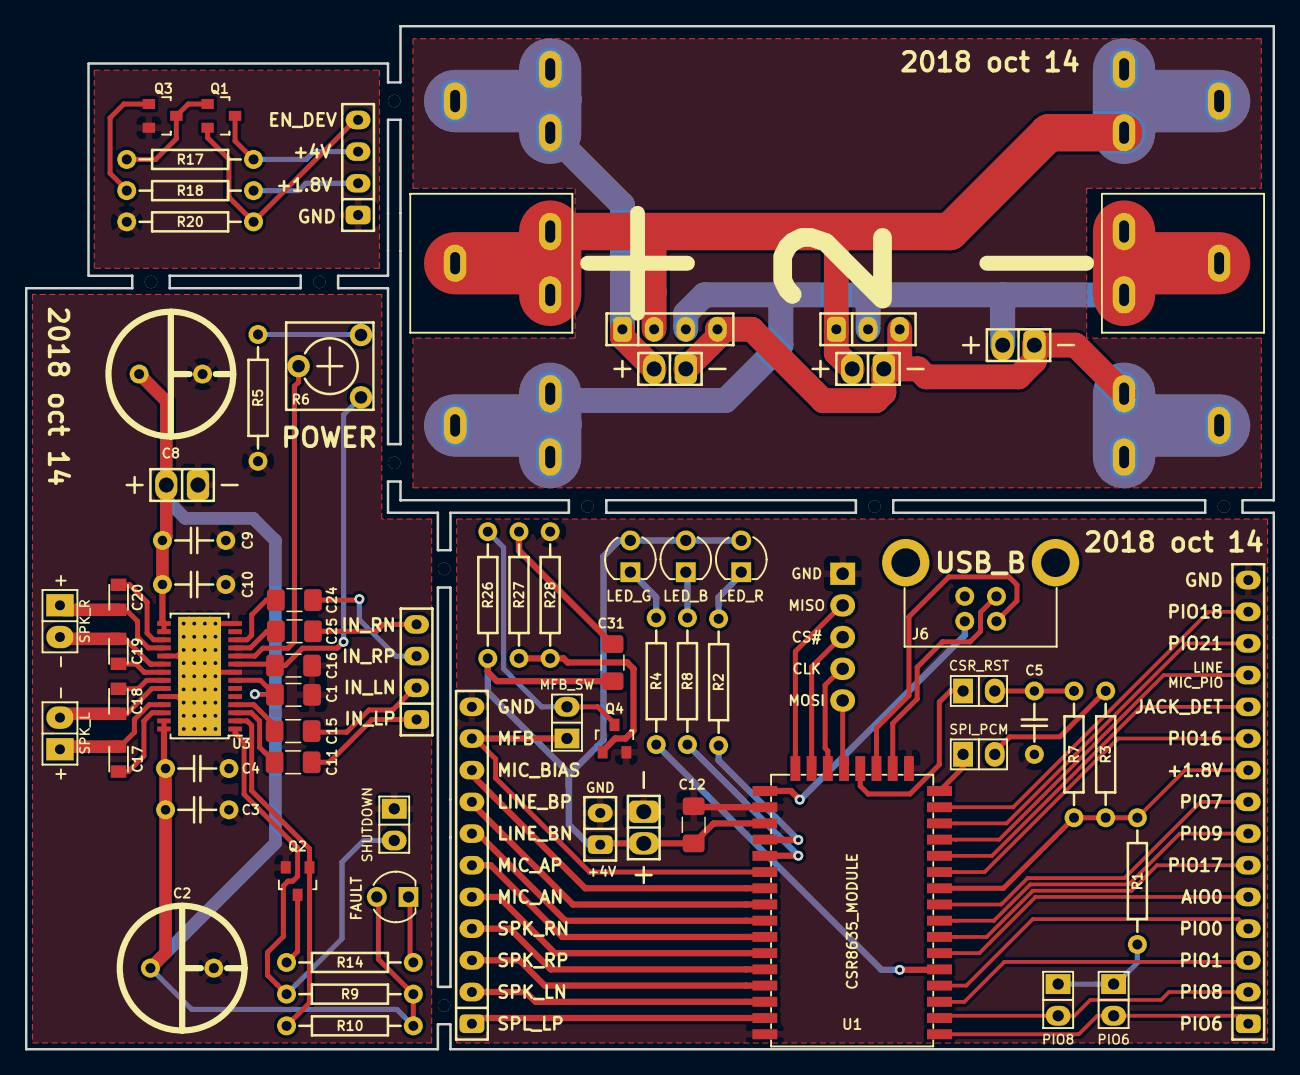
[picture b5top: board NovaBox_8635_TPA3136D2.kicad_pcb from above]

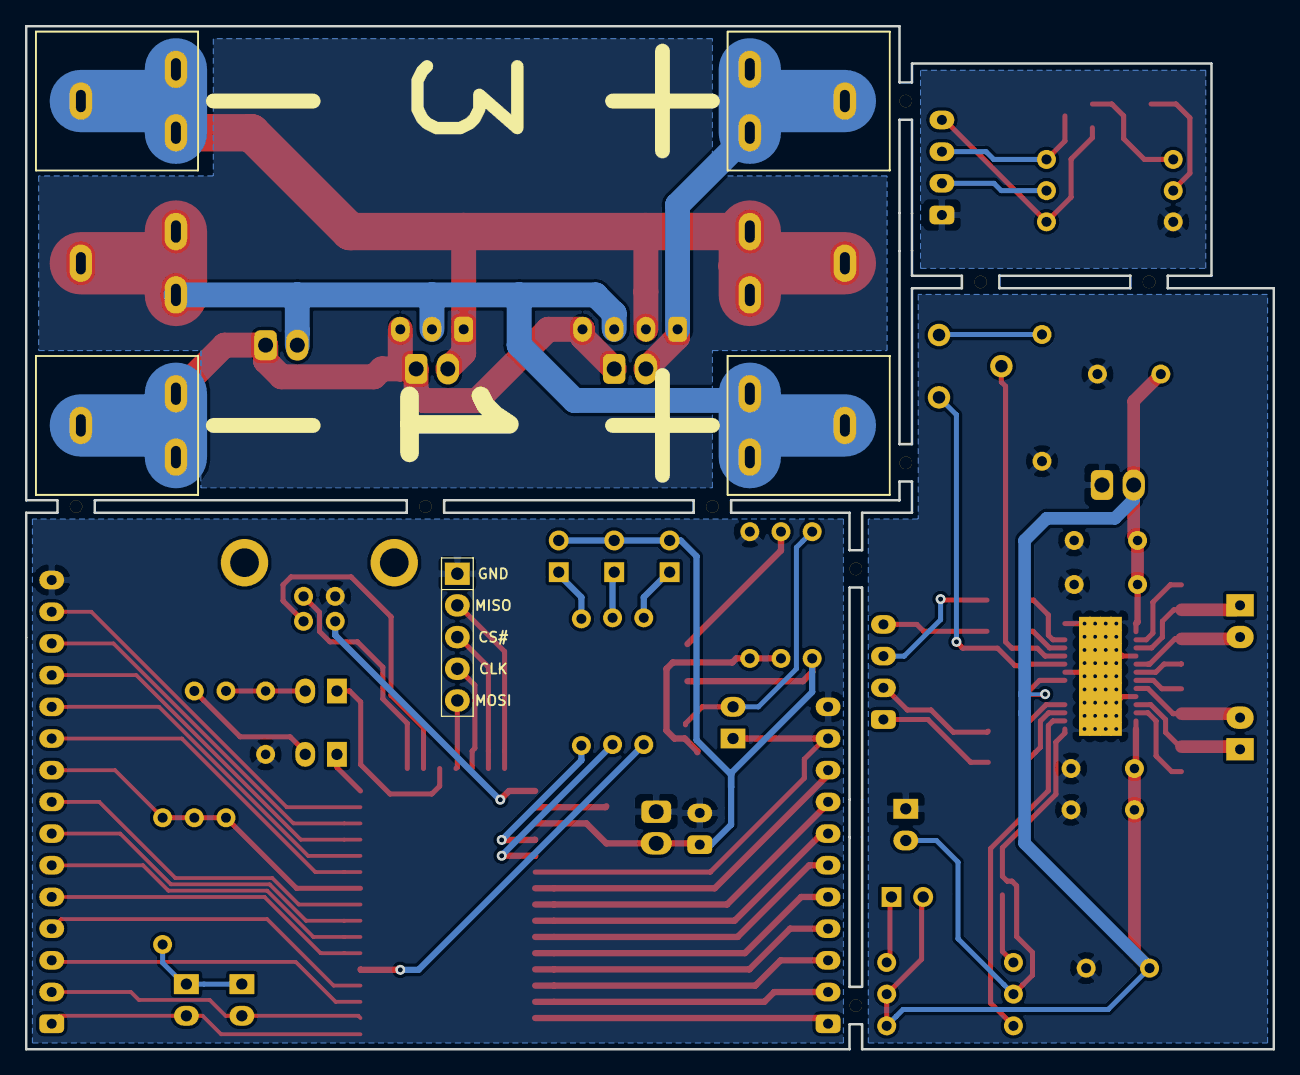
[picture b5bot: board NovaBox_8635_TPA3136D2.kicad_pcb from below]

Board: 2 copper layers, 100.0 x 82.0 mm, 71 parts (3 on the bottom side), 80 nets.

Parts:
BT1, BT2, BT3: 18650; Batt_Holder_18650_mini
C1, C11, C12, C15, C16, C24, C25, C31: 1uF; C_1206
C2, C8: 100uF; CPOL_D10_P4.5
C3, C5, C9: 100nF; C_5MM
C4, C10: 1nF; C_5MM
C17, C18, C19, C20: 220nF; C_0805
D1: LED_R; LED-3MM
D2: LED_G; LED-3MM
D3: FAULT; LED-3MM
D4: LED_B; LED-3MM
J1: CONN_01X11; PIN_11x1
J2: CONN_01X15; PIN_15x1
J3: CONN_01X02; PIN_2x1
J5, J9, J10, J12, J13: CONN_01X02; PWR
J6: USB_B
J7, J8, J14: CONN_01X04; PIN_4x1
J11: CONN_01X03; PIN_3x1
Q1, Q2: IRLML6401; SOT-23
Q3, Q4: MMBT3904; SOT-23
R1, R2, R4, R8, R27: 1K; R_10MM
R3, R7, R17, R18, R20, R26, R28: 10K; R_10MM
R5, R10: 10k; R_10MM
R6: 100k; RPOT_RKT6V
R9: 100k; R_10MM
R14: 1k; R_10MM
S1: SHUTDOWN; Switch_2.5mm
SPK1: SPK_L; SPKR
SPK2: SPK_R; SPKR
SW1: PIO8; Switch_2.5mm
SW2: PIO6; Switch_2.5mm
SW3: SPI_PCM; Switch_2.5mm
SW4: CSR_RST; Switch_2.5mm
SW5: MFB_SW; Switch_2.5mm
U1: CSR8635_MODULE
U2: CSR_DebugSmall
U3: TPA3136D2; HTSSOP-28_4.4x9.7mm_Pitch0.65mm_ThermalPad

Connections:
+1V8: J2.9, R1.2, R3.1, R7.1, U1.10
+4V: C12.1, C31.1, D1.2, D2.2, D4.2, J3.1, J5.1, R26.2, U1.27
+8V: C1.2, C2.1, C3.2, C4.2, C8.1, C9.2, C10.2, D3.2, J13.1, R9.2, R10.1, U3.7, U3.15, U3.16, U3.27, U3.28
/1.8V: J14.2, R18.2
/4V: J14.3, Q1.3, R17.1
/AIO0: J2.5, U1.6
/BAT1+: BT1.1, BT2.2, J8.3, J11.2, J12.1
/BAT2+: BT2.1, BT3.2, J8.2, J10.1, J11.1
/BAT3+: BT3.1, J8.1, J9.1
/BAT-: BT1.2, J8.4, J9.2, J10.2, J11.3, J12.2
/D+: J6.3, U1.18
/D-: J6.2, U1.19
/IN_LN: C15.1, J7.2
/IN_LP: C11.1, J7.1
/IN_RN: C25.1, J7.4
/IN_RP: C24.1, J7.3
/JACK_DET: J2.11, U1.12
/LINE_BN: J1.7, U1.33
/LINE_BP: J1.8, U1.32
/LINE_MIC_PIO: J2.12, U1.13
/MIC_AN: J1.5, U1.35
/MIC_AP: J1.6, U1.34
/MIC_BIAS: J1.9, U1.31
/PI016: J2.10, U1.11
/PIO0: J2.4, U1.4
/PIO1: J2.3, U1.3
/PIO7: J2.8, U1.9
/PIO9: J2.7, U1.8
/PIO17: J2.6, U1.7
/PIO18: J2.14, U1.15
/PIO21: J2.13, U1.14
/SPK_LN: J1.2, U1.38
/SPK_LP: J1.1, U1.39
/SPK_RN: J1.4, U1.36
/SPK_RP: J1.3, U1.37
CSR_RST: SW4.1, U1.20
EN_DEVICES: J14.4, Q1.2, R20.1
GND: C1.1, C2.2, C3.1, C4.1, C5.2, C8.2, C9.1, C10.1, C12.2, C16.1, J1.11, J2.15, J3.2, J5.2, J6.4, J13.2, J14.1, Q2.2, Q3.2, Q4.2, R5.2, R20.2, R28.1, S1.1, U1.17, U1.26, U1.40, U2.5, U3.8, U3.14, U3.19, U3.24, U3.29
LED_B: R8.1, U1.29
LED_G: R4.1, U1.5
LED_R: R2.1, U1.28
MFB: J1.10, SW5.1, U1.30
unnamed: C5.1, R7.2, SW4.2
unnamed: C11.2, U3.3
unnamed: C15.2, U3.4
unnamed: C16.2, R6.1, U3.9
unnamed: C17.1, SPK1.1, U3.25
unnamed: C17.2, U3.26
unnamed: C18.1, SPK1.2, U3.23
unnamed: C18.2, U3.22
unnamed: C19.1, SPK2.2, U3.20
unnamed: C19.2, U3.21
unnamed: C20.1, SPK2.1, U3.18
unnamed: C20.2, U3.17
unnamed: C24.2, U3.12
unnamed: C25.2, U3.11
unnamed: C31.2, R27.2
unnamed: D1.1, R2.2
unnamed: D2.1, R4.2
unnamed: D3.1, R14.1
unnamed: D4.1, R8.2
unnamed: Q1.1, Q3.3, R17.2
unnamed: Q2.1, R10.2, U3.2
unnamed: Q2.3, R14.2
unnamed: Q3.1, R18.1
unnamed: Q4.1, R27.1, R28.2
unnamed: Q4.3, R26.1, SW5.2
unnamed: R1.1, SW1.1, SW2.1
unnamed: R3.2, SW3.2
unnamed: R5.1, R6.3
unnamed: R6.2, U3.10
unnamed: R9.1, S1.2, U3.1
unnamed: U1.21, U2.1
unnamed: U1.22, U2.2
unnamed: U1.23, U2.3
unnamed: U1.24, U2.4
PIO6: J2.1, SW2.2, U1.1
PIO8: J2.2, SW1.2, U1.2
SPI_PCM: SW3.1, U1.16
VBUS: J6.1, U1.25

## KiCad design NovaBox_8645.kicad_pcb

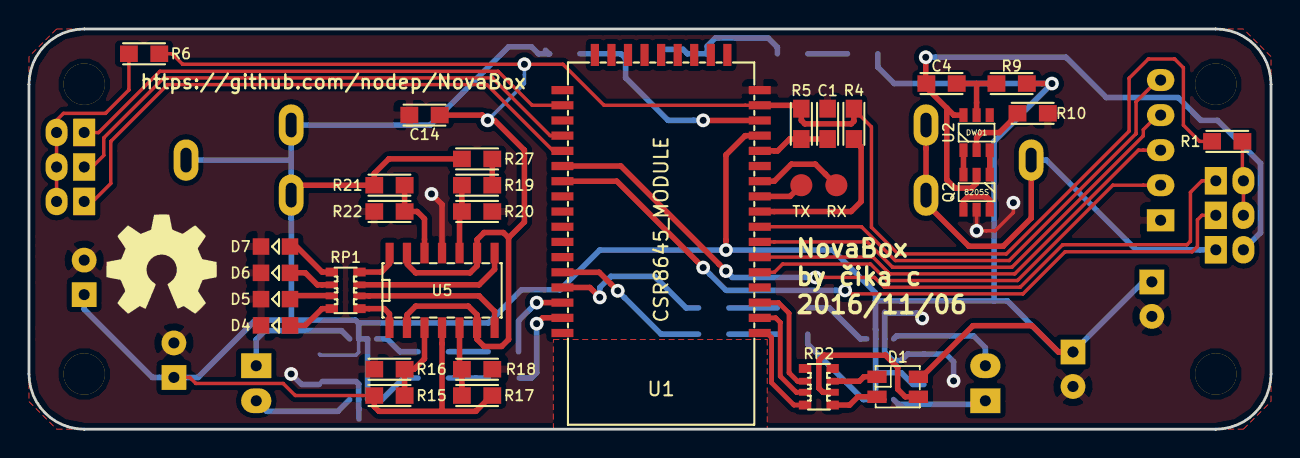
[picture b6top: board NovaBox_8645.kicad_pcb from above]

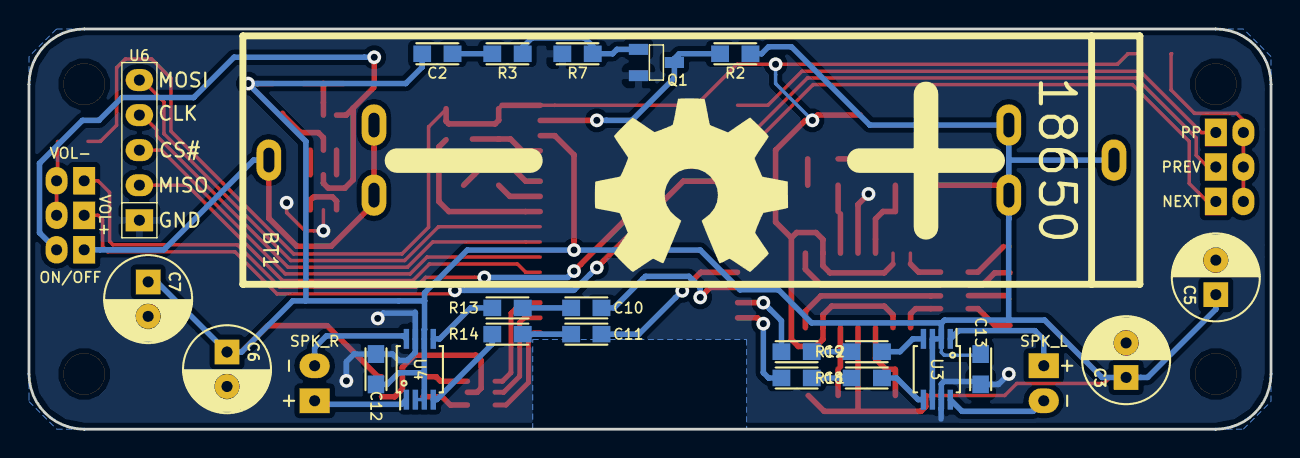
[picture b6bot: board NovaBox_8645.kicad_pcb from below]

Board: 2 copper layers, 90.0 x 29.0 mm, 66 parts (31 on the bottom side), 63 nets.

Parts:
BT1: 18650; Batt_Holder_18650
C1, C4, C8, C9, C10, C11, C14: 100nF; C_0805
C2, C12, C13: 1uF; C_0805
C3, C5, C6, C7: 100uF; C_Radial_D6.3_L11.2_P2.5
D1: LED_RABG_l; PLCC4
D4, D5, D6, D7: LEDV; LED-0805
P1, P3, P4, P5: MH; MountingHole
Q1: MMBT3904_l; SOT23
Q2: 8205S; SOT23_6
R1, R2, R4, R5, R6, R7: 10K; R_0805
R3, R10, R11, R12, R13, R14, R27: 1K; R_0805
R9: 100R; R_0805
R15, R19, R20: 43K; R_0805
R16, R18, R22: 36K; R_0805
R17: 39K; R_0805
R21: 33K; R_0805
RP1, RP2: 4x1K; Resistor_Array_x4_1206
S1: SPK_L; SPKR
S2: SPK_R; SPKR
SW2: NEXT; Switch_2mm
SW3: PREV; Switch_2mm
SW4: PP; Switch_2mm
SW5: VOL+; Switch_2mm
SW6: VOL-; Switch_2mm
SW7: ON/OFF; Switch_2mm
U1: CSR8645_MODULE
U2: DW01; SOT23_6
U3, U4: PAM8304; MSOP-8_0.65mmPitch
U5: MCP6004_l; SOIC-14_N
U6: CSR_DebugSmall
W1: TX; TestPad
W2: RX; TestPad

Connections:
1V8: C14.2, R1.1, R4.1, R5.1, R6.1, U1.16, U5.2, U5.6, U5.9, U5.13
+BATT: BT1.1, C2.1, C3.1, C5.1, C6.1, C7.1, C12.1, C13.1, D1.2, R2.2, R9.1, R15.2, R17.2, R21.2, R27.2, U1.14, U3.2, U3.3, U3.6, U4.2, U4.3, U4.6, U5.4
CSR_RST: C1.1, R5.2, U1.13
GND: C1.2, C3.2, C5.2, C6.2, C7.2, C12.2, C13.2, C14.1, D4.1, D5.1, D6.1, D7.1, Q1.2, Q2.5, R7.1, R10.1, R16.2, R18.2, R20.2, R22.2, U1.17, U3.7, U4.7, U5.11, U6.5
NEXT: SW2.1, U1.31
unnamed: BT1.2, SW7.1
unnamed: C2.2, R3.2
unnamed: C4.1, R9.2, U2.5
unnamed: C4.2, Q2.2, SW7.2, U2.6
unnamed: C8.1, R11.1
unnamed: C8.2, U1.42
unnamed: C9.1, R12.1
unnamed: C9.2, U1.41
unnamed: C10.1, R13.1
unnamed: C10.2, U1.40
unnamed: C11.1, R14.1
unnamed: C11.2, U1.39
unnamed: D1.1, RP2.3
unnamed: D1.3, RP2.2
unnamed: D1.4, RP2.1
unnamed: D4.2, RP1.8
unnamed: D5.2, RP1.7
unnamed: D6.2, RP1.6
unnamed: D7.2, RP1.5
unnamed: Q1.1, R3.1, R7.2
unnamed: Q2.1, U2.3
unnamed: Q2.3, U2.1
unnamed: Q2.4, Q2.6
unnamed: R1.2, SW5.2, SW6.2
unnamed: R6.2, SW2.2, SW3.2, SW4.2
unnamed: R10.2, U2.2
unnamed: R11.2, U3.5
unnamed: R12.2, U3.4
unnamed: R13.2, U4.5
unnamed: R14.2, U4.4
unnamed: R15.1, R16.1, U5.3
unnamed: R17.1, R18.1, U5.5
unnamed: R19.1, R20.1, U5.10
unnamed: R19.2, R27.1
unnamed: R21.1, R22.1, U5.12
unnamed: RP1.1, U5.1
unnamed: RP1.2, U5.7
unnamed: RP1.3, U5.8
unnamed: RP1.4, U5.14
unnamed: RP2.6, U1.3
unnamed: RP2.7, U1.2
unnamed: RP2.8, U1.1
unnamed: S1.1, U3.1
unnamed: S1.2, U3.8
unnamed: S2.1, U4.1
unnamed: S2.2, U4.8
unnamed: U1.5, U6.4
unnamed: U1.6, U6.3
unnamed: U1.7, U6.2
unnamed: U1.8, U6.1
unnamed: U1.10, W1.1
unnamed: U1.11, W2.1
PP/CALL: SW4.1, U1.28
PREV: SW3.1, U1.30
PWER_E: Q1.3, R2.1, U1.15
SPI_PCM: R4.2, U1.9
VOL+: SW5.1, U1.33
VOL-: SW6.1, U1.32
